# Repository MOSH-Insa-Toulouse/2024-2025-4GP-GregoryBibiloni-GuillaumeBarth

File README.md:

# 2024-2025-4GP-GregoryBibiloni-GuillaumeBarth

## Projet Capteur Graphite

# Sommaire

- [Contexte](#contexte)
- [Livrables](#livrables)
- [Matériel necéssaire](#matériel-nécessaire)
- [Simulation LTSpice](#simulation-ltspice)
- [Design du PCB via KiCad](#design-du-pcb-via-kicad)
- [Réalisation du Shield](#réalisation-du-shield)
- [Code Arduino](#code-arduino)
- [Application mobile Android via MIT App Inventor](#application-mobile-android-via-mit-app-inventor)
- [Banc de test et analyse](#banc-de-test-et-analyse)
- [Datasheet du capteur graphite](#datasheet-du-capteur-graphite)
- [Conclusion](#conclusion)

---

# Contexte

Ce projet est réalisé dans le cadre de l’UF « du capteur au banc de test » pour les étudiants en quatrième année Génie Physique. Nous nous sommes inspirées de l’article scientifique _Pencil Drawn Strain Gauges and Chemiresistors on Paper_ (Cheng-Wei Lin, Zhibo Zhao, Jaemyung Kim & Jiaxing Huang).
Cet article explique comment faire un capteur résistif à partir de crayon et de papier.

Quand on écrit avec un crayon gris sur du papier, on dépose des couches de graphites qui sont des conducteurs et laisse passer le courant mais avec une résistance. En déformant ce papier, les chaines de graphique sont plus ou moins éloignés et le courant circule plus ou moins facilement ce qui implique une variation de résistance. Ce phénomène fait qu’on peut faire de ce capteur une jauge de contrainte.

_Cette figure vient de l'article cité ci dessus, et montre les chaines de carbone si on effectue une compression ou une flexion du papier. Une compression fait qu'on a des chaines plus proche donc une plus faible valeur de résistance. Pour une flexion on a l'effet contraire_

L’objectif de ce projet est donc de pouvoir réaliser une jauge de contrainte « low-tech » 

---

# Livrables

Voici la liste des livrables :

•	Le Shield PCB branché sur une carte Arduino UNO, intégrant le capteur graphite, un module Bluetooth, un encodeur rotatoire, un potentiomètre numérique, un écran OLED, et un capteur de flexion industriel.

•	Le code Arduino qui permet de contrôler tous les composants et d’acquérir les mesures. (Mesure de résistance, Connection Bluetooth, Affichage de l’OLED, l’encodeur rotatoire et le potentiomètre numérique).

•	L’application Android qui permet d’afficher la valeur de la résistance directement sur son téléphone.

•	La datasheet du capteur en graphite (avec différentes valeurs de crayon).

---

# Matériel nécessaire

Pour concevoir notre dispositif, on a besoin de ces composants :

•	Des résistances : 1 résistance de 1 kΩ, 1 résistance de 10 kΩ, 2 résistances de 100 kΩ, une résistance R2 qui correspond au potentiomètre numérique (le MCP41050) et une résistance de 47 kΩ pour la jauge de contrainte industrielle.

•	Des capacités : 2 capacités de 100 nF et 1 de 1 µF.

•	D’un amplificateur opérationnel : le LTC1050.

•	Un module Bluetooth HC-05.

•	Un encodeur rotatoire ESP32.

•	Un écran OLED 128 * 64.

•	Un flex sensor.

•	Le capteur graphite (connecté avec des pinces croco) fait avec un papier et un crayon.

•	La carte Arduino UNO.

---

# Simulation LTSpice

La résistance interne du capteur graphite est de l’ordre du GΩ donc le courant généré après application de la tension de 5V (Valeur de l’arduino) est faible (de l’ordre du nA). On a besoin de l’amplifier grâce à un montage transimpédance composé d’un amplificateur opérationnel (AOP), le LTC1050, qui peut capter les signaux de faible intensité.

Ce montage est composé de 3 filtres afin de limiter le bruit :

•   En rouge, on filtre le 50 Hz du réseau d’électricité

•	En bleu, on filtre le bruit du capteur

•	En vert, on filtre le bruit de l’acquisition de l’Arduino

Voici une simulation sur LTSpice qui montre l'atténuation du bruit en fonction de la fréquence :

On réduit le 50 Hz de 72 dB environ.

Pour calculer la valeur de la résistance du capteur graphite, la formule est la suivante :

Où R2 correspond à la valeur du potentiomètre numérique.

---

# Design du PCB

On a conçu notre PCB via le logiciel KiCad, cela s’est fait en 2 étapes :

La première étape consiste en la réalisation du schématique, donc de créer tous les composants qu’on utilise en leur attribuant des pins, un nom et un modèle 3D. Une fois tous nos composants créés, on rajoute le montage de notre amplificateur transimpédance et on affecte chaque pin de l’Arduino à nos composants et on effectue le câblage entre les différents composants.

Ceci est le schéma électrique de l'ensemble de nos composants.

Une fois cela fait, on doit maintenant positionner l'ensemble de nos composants sur le PCB et les relier par la suite. Il faut placer judicieusement les composants sur le PCB afin qu'ils ne se chevauchent pas les uns sur les autres, et qu'ils n'empêchent pas le câblage de l'ensemble des composants. Cette étape nécessite une certaine rigueur afin d'éviter le plus que possible de faire des VIA (trou effectué afin de faire des connexions par-dessus certains routages).

Voici le résultat de notre routage sur notre PCB :

U6 correspond à l’encodeur rotatoire (et le servor a été mit en plus si on avait besoin d’un servo motor pendant les manipulations).

👉 [Voici le lien pour le KiCad](KiCad/)

---

# Réalisation du Shield

Une fois le PCB réalisé sur KiCaD, on l'a envoyé à Cathy afin qu'elle puisse vérifier que le PCB est correct et prêt à être imprimé. Pour cela, on lui a envoyé notre Gerber, le schéma contenant que le routage de notre carte. Le Gerber sert de masque afin de faire une impression UV sur une couche en cuivre sur la carte en époxy. Une fois cette impression faite, elle a plongé la plaque dans un révélateur qui a retiré les zones non exposées. Enfin un lavage à l'acétone permet d'enlever les dernières impuretés.

Le Gerber :

Il faut par la suite percer des trous sur notre plaque avec un fôret (0.8mm pour les composants et 1mm pour les pins de l’Arduino).

Une fois cette étape effectuée, on place tous nos composants sur notre Shield en les soudants, puis on raccorde le Shield avec la carte Arduino Uno :

---

# Code Arduino

On code maintenant le programme qui permet de faire fonctionner notre système. Dans ce code on peut contrôler un menu qui s’affiche sur l’écran OLED à l’aide de l’encodeur rotatoire. On peut rentrer manuellement la valeur du potentiomètre numérique à l’aide de ce menu, on peut contrôler la connexion Bluetooth et on peut lire la valeur de la résistance liée à la déformation du capteur.

Le code est présent dans notre Git.
👉 [Voici le lien pour le code Arduino](Code%20Arduino/)

---

# Application mobile Android via MIT App Inventor

On a créé l’application grâce au logiciel MIT App Inventor. C’est un APK et il est composé d’une face avant et d’une face arrière : 

Ceci est la face avant.

Et ceci est la face arrière.

Grâce à cette application, on peut se connecter sur le module Bluetooth et récupérer la valeur de la résistance en fonction de la flexion.

👉 [Voici le lien pour l'application Android (sous forme .aia et .apk)](Application%20Android/)

---

# Banc de test et analyse

On veut faire un banc de test qui permet de calculer la valeur de la résistance du capteur graphite pour différentes valeurs de déformation.
On utilise donc un support qui possèdent différents emplacement qui ont chacun leur propre rayon de courbure.

Le support ressemble à :

De haut en bas :

•   Rayon de courbure de 0.045m pour une déformation de 2,11E-3. 

•   Rayon de courbure de 0.04m pour une déformation de 2,38E-3.

•   Rayon de courbure de 0.035m pour une déformation de 2,71E-3.

•   Rayon de courbure de 0.03m pour une déformation de 3,17E-3.

•   Rayon de courbure de 0.025m pour une déformation de 3,80E-3.

•   Rayon de courbure de 0.02m pour une déformation de 4,75E-3.

Voici les résultats obtenus avec une résistance du potentiomètre de 40906 ohms :  

Valeur obtenue pour six types de crayons en effectuant une flexion : HB, HB-2, 2B, 3B, 6B et B.
On remarque donc une augmentation de la résistance relative plus on déforme le papier, ce qui était le résultat attendu. Mais le résultat n'est pas linéraire.

Valeur obtenue pour cinq types de crayons en effectuant une compression : HB, HB-2, 2B, 3B et 6B.
On remarque donc une diminution de la résistance relative plus on déforme le papier, ce qui était le résultat attendu. Encore une fois le résultat n'est pas linéaire et on n'arrive pas à obtenir des valeurs avec le crayon B.

On a remarqué un défaut pendant nos manipulations, et c'est que le papier s'use très vite et on a souvent besoin de le changer fréquemment afin qu'il soit de nouveau opérationnel. 

---

# Datasheet du capteur graphite

👉 [Voici le lien pour la data sheet](DataSheet/DataSheet.pdf)

---

# Conclusion

En conclusion, ce capteur permet de mesurer des variations de résistance et donner un ordre de grandeur de cette variation. Mais il n'est pas très précis et il s'use facilement. Il ne permet donc pas de remplacer le flex sensor industriel

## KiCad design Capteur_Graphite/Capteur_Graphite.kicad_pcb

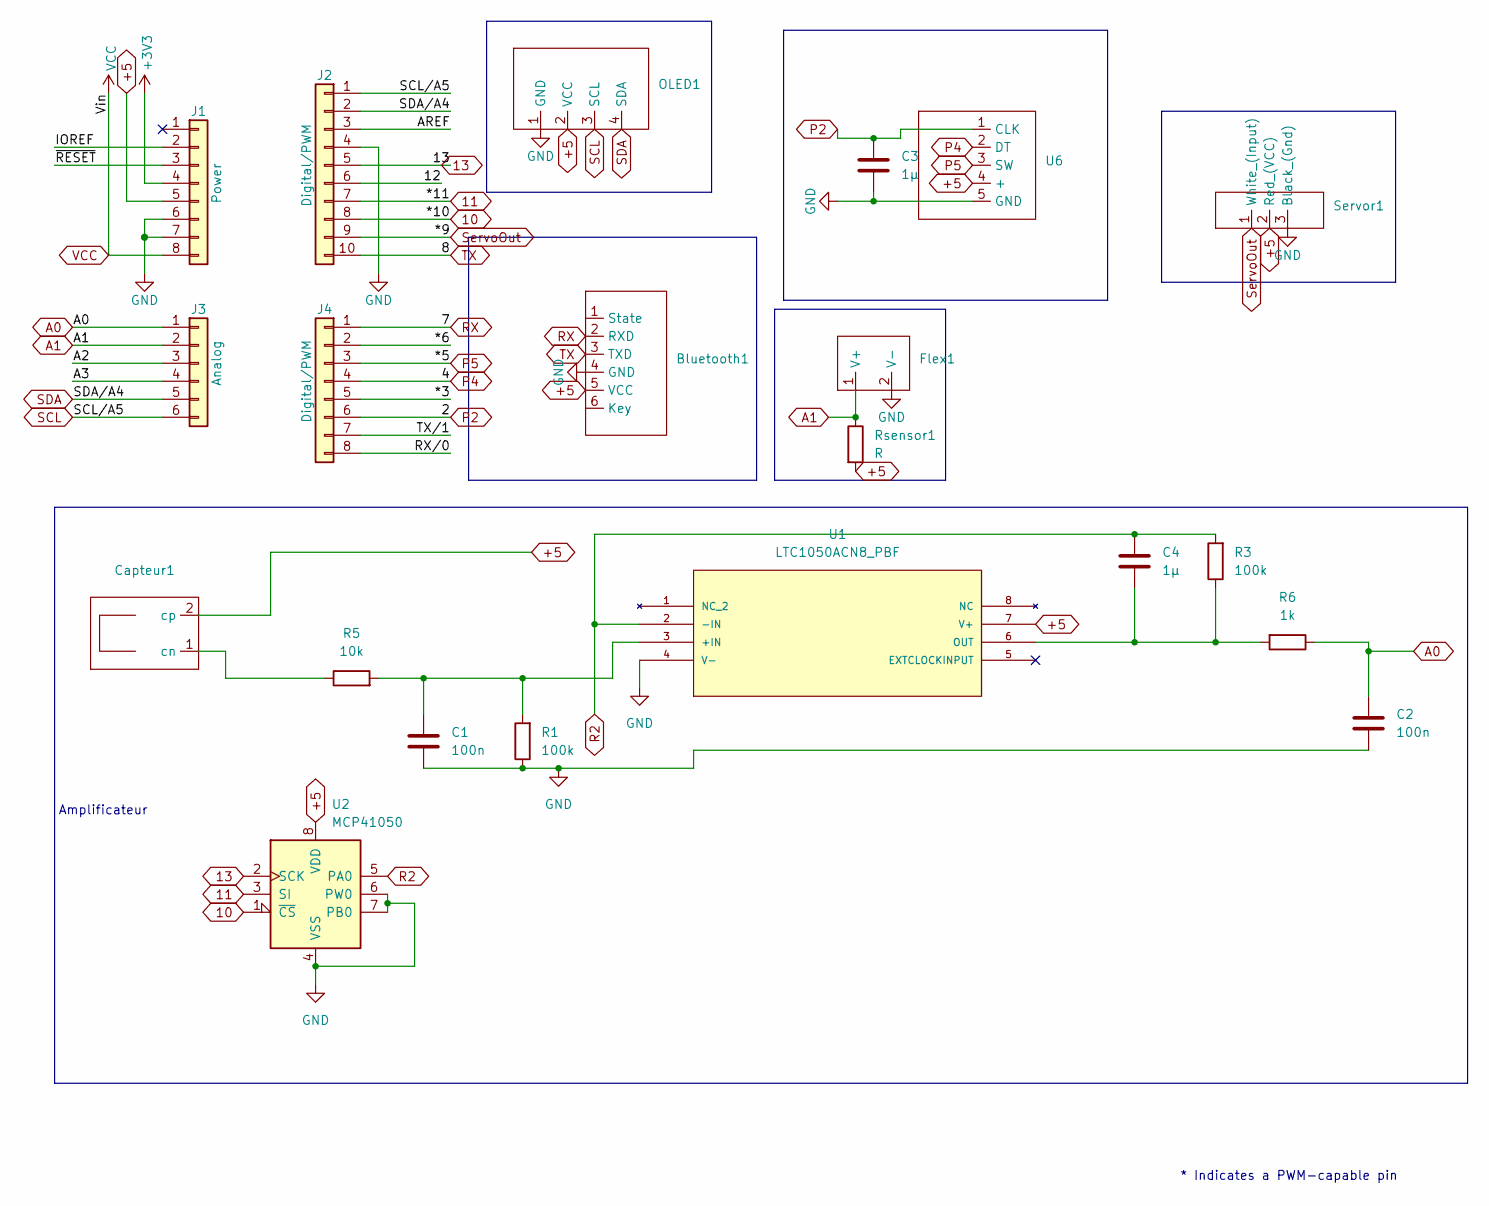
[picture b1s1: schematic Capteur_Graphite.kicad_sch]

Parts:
Bluetooth1: Bluetooth
C1, C2: 100n; C_Disc_D5.0mm_W2.5mm_P5.00mm
C3, C4: 1µ; C_Rect_L7.0mm_W4.5mm_P5.00mm
Capteur1: CapteurGraph
Flex1: FlexSensor
J1: Power; PinSocket_1x08_P2.54mm_Vertical
J2: Digital/PWM; PinSocket_1x10_P2.54mm_Vertical
J3: Analog; PinSocket_1x06_P2.54mm_Vertical
J4: Digital/PWM; PinSocket_1x08_P2.54mm_Vertical
OLED1: OLED
R1, R3: 100k; R_Axial_DIN0309_L9.0mm_D3.2mm_P5.08mm_Vertical
R5: 10k; R_Axial_DIN0309_L9.0mm_D3.2mm_P5.08mm_Vertical
R6: 1k; R_Axial_DIN0309_L9.0mm_D3.2mm_P5.08mm_Vertical
Rsensor1: R; R_Axial_DIN0204_L3.6mm_D1.6mm_P1.90mm_Vertical
Servor1: ServoMotor
U1: LTC1050ACN8_PBF; LTC1050; MANUFACTURER_PART_NUMBER ltc1050acn8
U2: MCP41050; LTC1050
U6: Rotatoire

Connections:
10: J2.8, U2.1 (~CS)
11: J2.7, U2.3 (SI)
13: J2.5, U2.2 (SCK)
+3V3: J1.4
+5: Bluetooth1.5 (VCC), Capteur1.2 (cp), J1.5, OLED1.2 (VCC), Rsensor1.2, Servor1.2 (Red_(VCC)), U1.7 (V+), U2.8 (VDD), U6.4 (+)
/12: J2.6
/*3: J4.5
/*6: J4.2
/A2: J3.3
/A3: J3.4
/AREF: J2.3
/IOREF: J1.2
/RX/0: J4.8
/TX/1: J4.7
/~RESET: J1.3
A0: C2.1, J3.1, R6.1
A1: Flex1.1 (V+), J3.2, Rsensor1.1
GND: Bluetooth1.1 (State), Bluetooth1.4 (GND), Bluetooth1.6 (Key), C1.2, C2.2, C3.2, Flex1.2 (V-), J1.6, J1.7, J2.4, OLED1.1 (GND), R1.1, Servor1.3 (Black_(Gnd)), U1.4 (V-), U1.5 (EXTCLOCKINPUT), U2.4 (VSS), U2.6 (PW0), U2.7 (PB0), U6.5 (GND)
unnamed: Capteur1.1 (cn), R5.1
unnamed: C1.1, R1.2, R5.2, U1.3 (+IN)
unnamed: C4.2, R3.1, R6.2, U1.6 (OUT)
P2: C3.1, J4.6, U6.1 (CLK)
P4: J4.4, U6.2 (DT)
P5: J4.3, U6.3 (SW)
R2: C4.1, R3.2, U1.2 (-IN), U2.5 (PA0)
RX: Bluetooth1.2 (RXD), J4.1
SCL: J2.1, J3.6, OLED1.3 (SCL)
SDA: J2.2, J3.5, OLED1.4 (SDA)
ServoOut: J2.9, Servor1.1 (White_(Input))
TX: Bluetooth1.3 (TXD), J2.10
VCC: J1.8

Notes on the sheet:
Amplificateur
* Indicates a PWM-capable pin

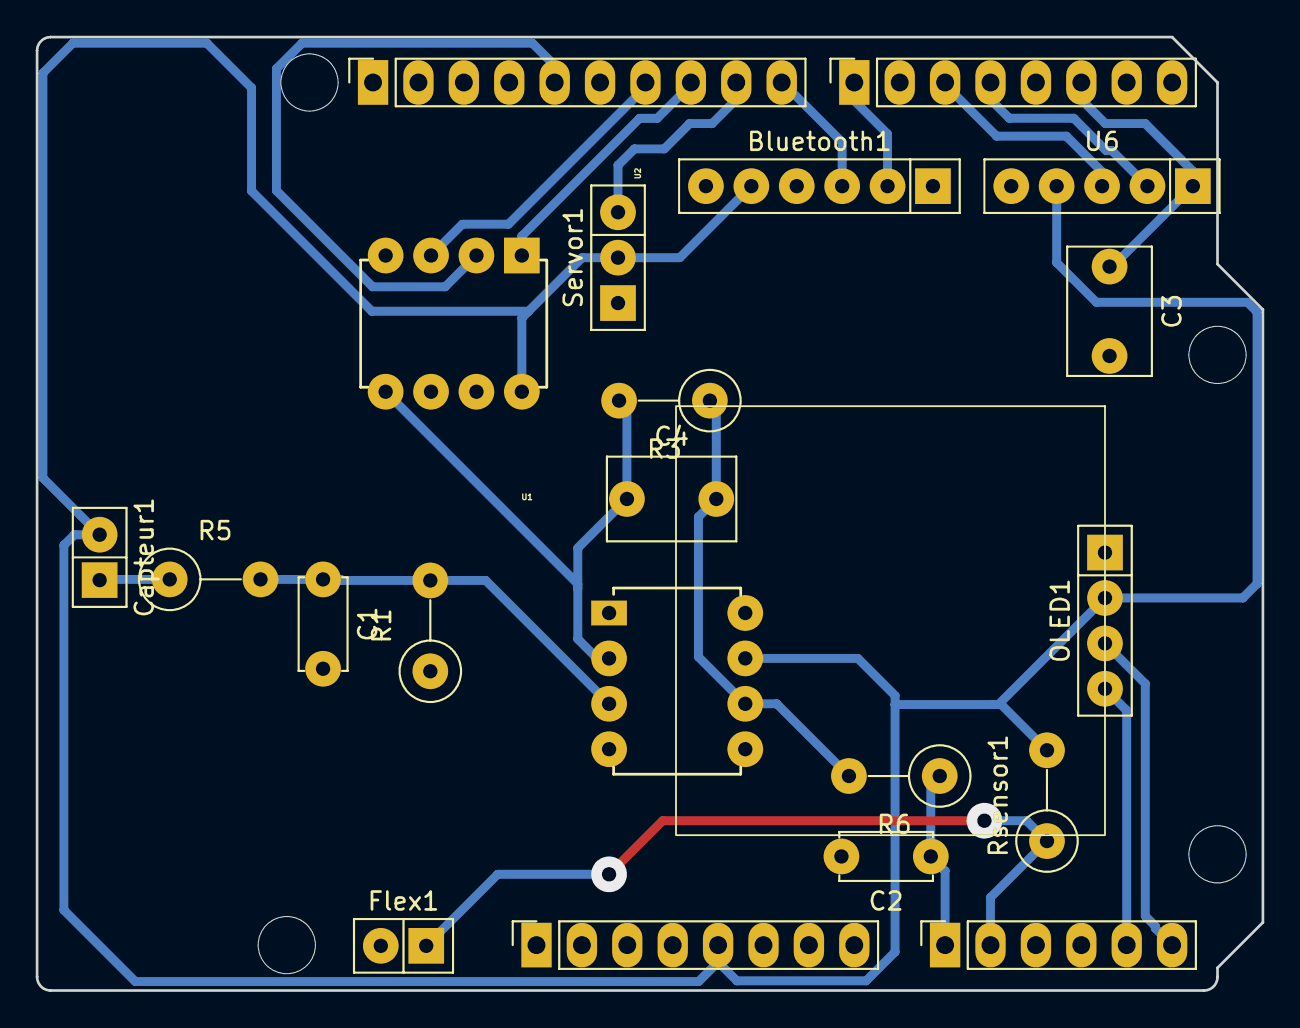
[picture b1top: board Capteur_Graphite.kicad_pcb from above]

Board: 2 copper layers, 68.6 x 53.3 mm, 25 parts (0 on the bottom side), 19 nets.

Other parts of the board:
MH1, MH2, MH3, MH4: MountingHole_3.2mm

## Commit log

2025-02-19 Ajout de ma todo liste
2025-02-19 Ajout du test
2025-02-19 Ajout dossier branche secondaire
2025-02-19 Test ajout branche
2025-02-19 Test thrid branchhhhh
2025-03-13 Organisation du projet sur Github
2025-03-13 Clear PCB
2025-03-13 Schematique propre
2025-03-13 Fin de séance du 13 mars
2025-03-14 PCB fini
2025-03-17 ajout lib symbol + retouche kicad_pcb
2025-03-17 Version Final du PCB + Gerber
2025-03-25 Version Final corrigée du PCB
2025-03-25 Finale 3 GND connecté
2025-03-25 Version Finale 4 le retour
2025-03-25 repositionement 3D
2025-03-31 tri fichier obsolete
2025-05-14 Contexte et sommaire
2025-05-14 Rubrique + simu
2025-05-15 Rajout de texte
2025-05-15 Forme
2025-05-15 position texte image
2025-05-15 Propre sur le Git
2025-05-15 Test.
2025-05-15 propre
2025-05-15 propre2
2025-05-15 Ajout du code arduino
2025-05-15 Nouveau ajout
2025-05-15 Modif
2025-05-15 Ca va marcher là
2025-05-15 Test
2025-05-15 C'est bon
2025-05-15 Rajout de l'application
2025-05-15 Rajout dans le test simple de la conversion en mV et pas en byt
2025-05-15 Schéma reduction bruit
2025-05-17 Correct
2025-05-18 La fin
2025-05-20 correction
2025-05-20 Ajourt android

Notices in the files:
parts and their libraries:
COPYRIGHT: Copyright C 2016 Accelerated Designs. All rights reserved
